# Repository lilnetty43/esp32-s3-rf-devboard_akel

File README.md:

# ESP32-S3 4-Layer RF Development Board

This project is a custom 4-layer development board built around the ESP32-S3. I designed the board to expand my PCB design experience into an RF-aware layout, multi-layer stackup design, controlled-impedance USB routing, and manufacturing preparation.

My board include native USB-C programming and power, 5 V-to-3.3 V regulation, GPIO breakout headers, BOOT and RESET controls, protection circuitry, test points, and a programmable RGB status LED.

*KiCad-generated 3D render of the ESP32-S3 development board.*

---

## Project Overview

The ESP32-S3 module provides Wi-Fi and Bluetooth connectivity using its integrated PCB antenna. The board exposes the ESP32-S3 GPIO through two headers while providing the supporting power, USB, programming, reset, and protection circuitry needed for standalone development.

A 4-layer PCB stackup was used to provide dedicated ground and power planes while maintaining short return paths and supporting controlled-impedance routing for the native USB interface.

---

## Details

- **MCU:** ESP32-S3 [LINK]
- **PCB:** 4-layer, 1.6 mm
- **USB:** USB-C with native ESP32-S3 USB programming[LINK]
- **USB Routing:** 90 Ω differential impedance target for D+/D−
- **Power Input:** 5V USB
- **Regulation:** 5V to 3.3V using LD1117S33 [LINK]
- **GPIO:** Dual breakout headers
- **Controls:** BOOT/RESET pushbuttons [LINK]
- **Protection:** USB ESD protection [LINK]
- **Status:** Programmable RGB LED [LINK]
- **Debugging:** Dedicated test points for important power and signal nets for debugging/checking

---

## PCB Stackup

The board uses a 4-layer stackup:
- **L1/F.Cu:** Components and signals
- **L2/In1.Cu:** Solid GND
- **L3/In2.Cu:** 3.3 V power 
- **L4/B.Cu:** Secondary signal routing

The stackup was configured around the intended JLCPCB manufacturing process rather than using KiCad's default layer construction.

---

## PCB Design Highlights [FIX!!!]

*Top PCB layout showing component placement and routed signals.*

---

## USB Differential Pair

The ESP32-S3 native USB interface was one of the primary high-speed layout considerations for this project.

The D+ and D− pair was routed using dimensions calculated for the selected 4-layer manufacturing stackup:

- **Target differential impedance:** 90 Ω
- **Reference plane:** L2 / In1.Cu GND
- **Routing layer:** L1 / F.Cu
- **Trace width:** 0.3051 mm
- **Pair spacing:** 0.1501 mm
- **Series termination:** 22 Ω

I utilized the JLCPCB resources and calculator to help determine this targeted impedance.

*USB D+ and D− differential-pair routing between the USB-C interface and ESP32-S3.*

---

## Tools

- KiCad — schematic capture, PCB layout, routing, and 3D visualization
- JLCPCB impedance calculator (USB differential-pair geometry)
- Manufacturer datasheets and reference designs
- Git/GitHub
---

## Manufacturing

The PCB design and manufacturing files have been prepared for fabrication through JLCPCB.

Manufacturing/order status: **Pending**

---

## What I Learned

This was a fun project to dive into. i have expanded on my previous PCB work by introducing new design factors like:

- Working with an RF module and PCB antenna keepout requirements
- Revisiting USB differential-pair routing and controlled impedance
- Revisiting the design around dedicated internal ground and power planes
- Applying manufacturer-specific PCB constraints
- Preparing a complete PCB design for external fabrication

---

## Repo Structure

```text
esp32-s3-rf-devboard/
├── README.md
├── docs/
│   └── images/
│       ├── 3d_renders/
│       ├── pcb_routing/
│       └── schematic/
├── fabrication/
│   └── JLCPCB_REV1/
├── hardware/
│   ├── ESP32S3_RF_DevBoard.kicad_pro
│   ├── ESP32S3_RF_DevBoard.kicad_sch
│   └── ESP32S3_RF_DevBoard.kicad_pcb
└── manufacturing (PENDING)/

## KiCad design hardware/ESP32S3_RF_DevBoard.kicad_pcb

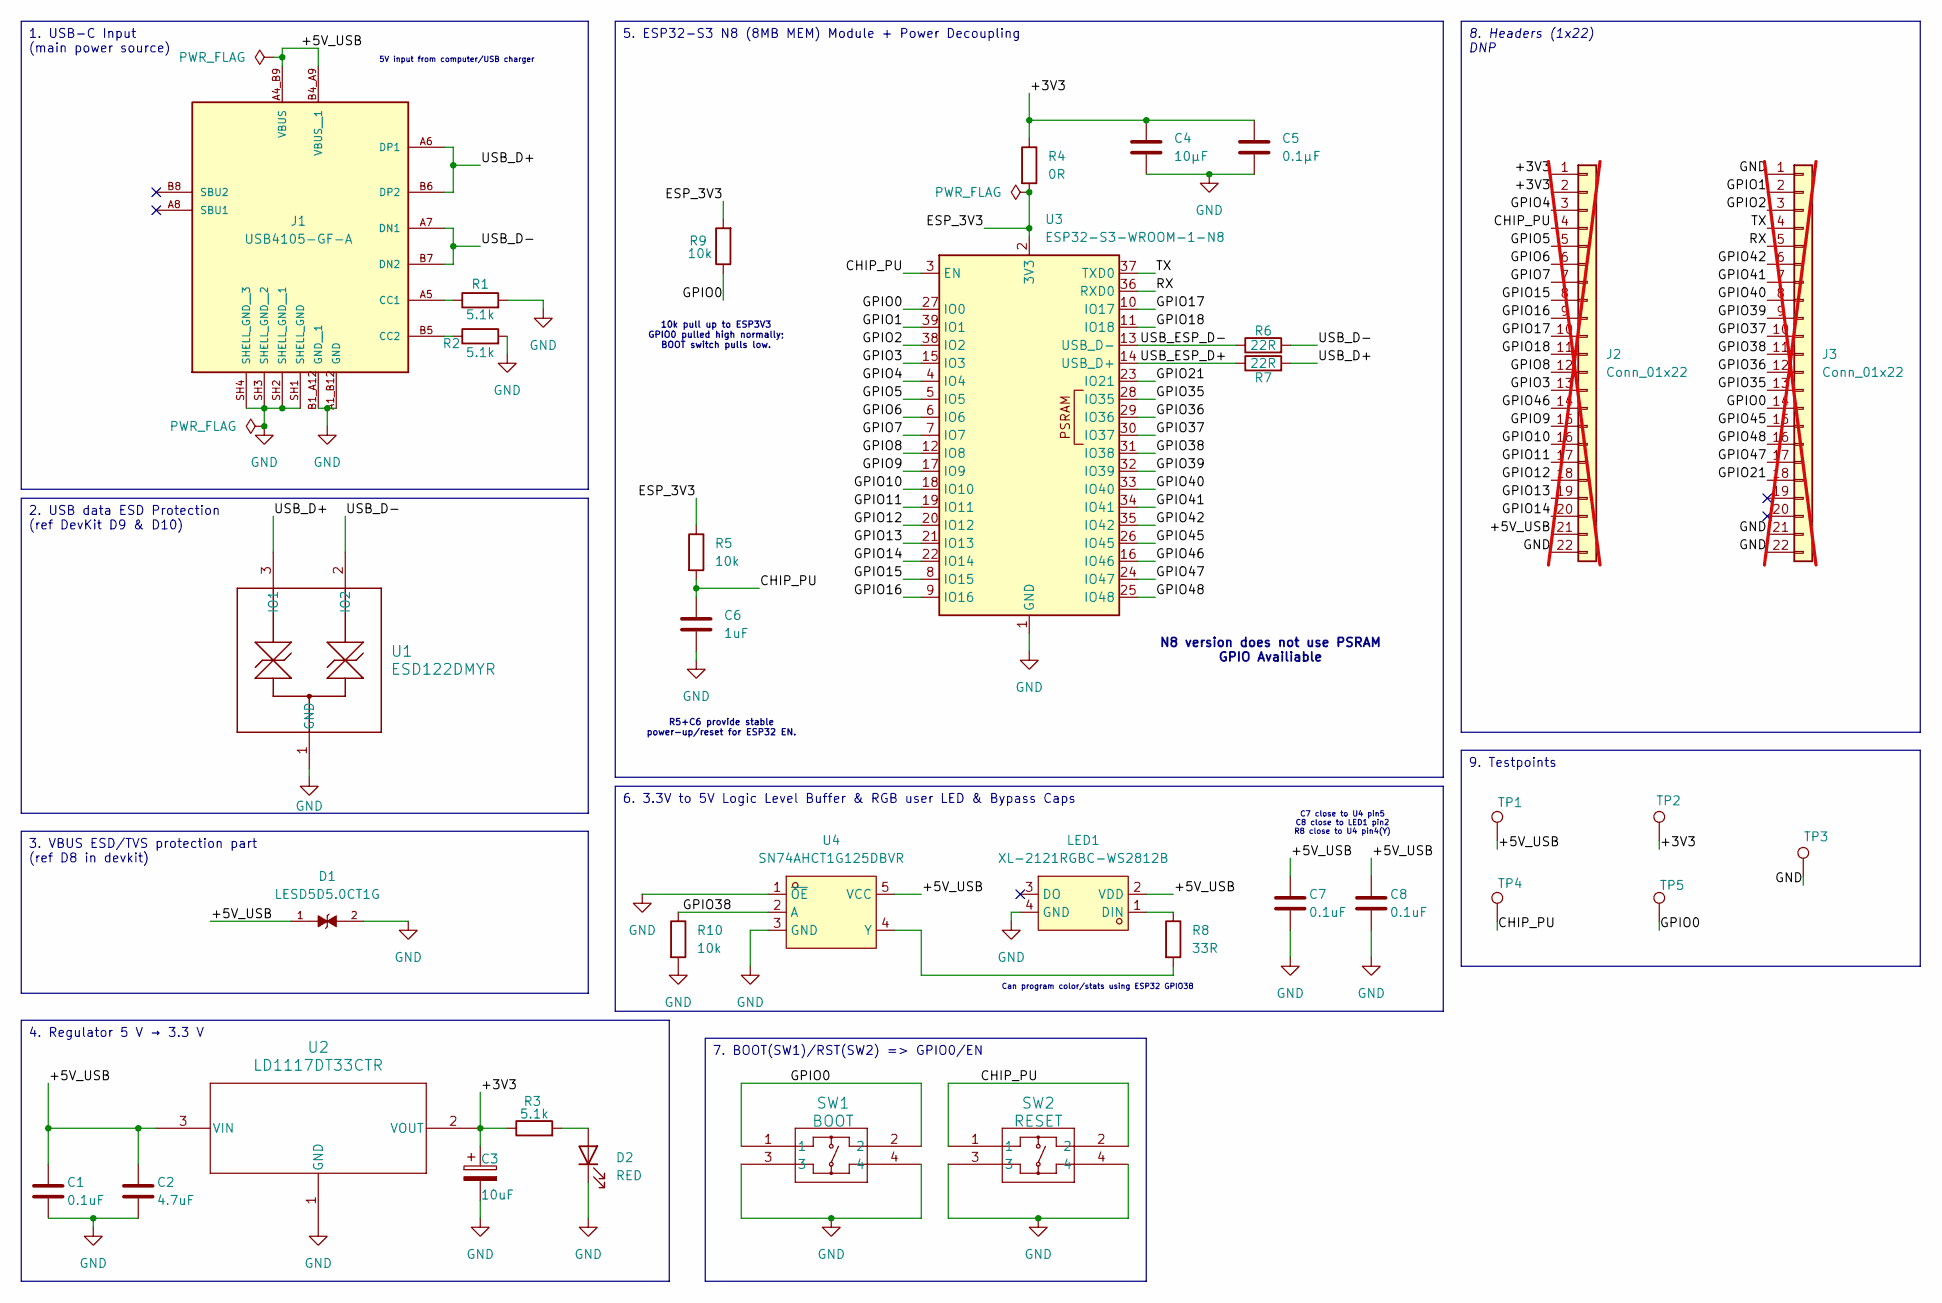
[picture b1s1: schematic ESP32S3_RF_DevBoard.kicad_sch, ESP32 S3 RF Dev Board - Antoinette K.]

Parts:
C1, C7, C8: 0.1uF; C_0603_1608Metric; MPN 0603B104K160CT; LCSC C80516
C2: 4.7uF; C_0805_2012Metric; MPN FS21B475K160EIG; LCSC C2929196
C3: 10uF; CP_EIA-3528-21_Kemet-B; MPN T491B106M016AT; LCSC/JLCPCB C118754
C4: 10µF; C_0603_1608Metric; Voltage 25V; Tolerance ±20%; MPN GRM188R61E106MA73D; LCSC/JLCPCB C91606
C5: 0.1µF; C_0603_1608Metric; Voltage 50V; Tolerance ±10%; MPN CL10B104KB8NNNC; LCSC/JLCPCB C1591
C6: 1uF; C_0805_2012Metric; Voltage 16V; Tolerance ±10%; MPN CL21B105KOFNNNE; LCSC/JLCPCB C24123
D1: LESD5D5.0CT1G; TVS_LESD5D5.0CT1G; PARTREV O
D2: RED; LED_0603_1608Metric; MPN KT-0603R; LCSC/JCLPCB C2286
J1: USB4105-GF-A; GCT_USB4105-GF-A; PARTREV B4
J2, J3: Conn_01x22; PinHeader_1x22_P2.54mm_Vertical; MPN PZ254V-11-22P; JLCPCB/LCSC C22465881; not fitted
LED1: XL-2121RGBC-WS2812B; LED-SMD_4P-L2.1-W2.1-BR_XL-2121RGBC-WS2812B; MPN XL-2121RGBC-2812B; LCSC Part C5349957
R1, R2: 5.1k; R_0603_1608Metric; JLCPCB/LCSC C14677
R3: 5.1k; R_0603_1608Metric; Tolerance ±5%
R4: 0R; R_0603_1608Metric; LCSC/JLCPCB C21189
R5, R9, R10: 10k; R_0603_1608Metric; MPN 0603WAF1002T5E; LCSC/JLCPCB C25804
R6, R7: 22R; R_0603_1608Metric; Tolerance ±1%; MPN 0603WAF220JT5E; LCSC/JLCPCB C23345
R8: 33R; R_0603_1608Metric; MPN 0603WAF330JT5E; LCSC/JLCPCB C23140
SW1: BOOT; SKRPANE010_AAL; MPN SKRPANE010; JLCPCB/LCSC C470426
SW2: RESET; SKRPANE010_AAL; MPN SKRPANE010; JLCPCB/LCSC C470426
TP1, TP2, TP3: TestPoint; TestPoint_Pad_D1.5mm
TP4, TP5: TestPoint; TestPoint_Pad_D1.0mm
U1: ESD122DMYR; DMY0003A
U2: LD1117DT33CTR; DPAK_STM
U3: ESP32-S3-WROOM-1-N8; ESP32-S3-WROOM-1
U4: SN74AHCT1G125DBVR; SOT-23-5_L3.0-W1.7-P0.95-LS2.8-BR; MPN SN74AHCT1G125DBVR; LCSC Part C7484

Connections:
/+3V3: C3.1, C4.1, C5.1, J2.1, J2.2, R3.1, R4.1, TP2.1 (1_1), U2.2 (VOUT)
/+5V_USB: C1.1, C2.1, C7.1, C8.1, D1.1, J1.A4_B9 (VBUS), J1.B4_A9 (VBUS__1), J2.21, LED1.2 (VDD), TP1.1 (1_1), U2.3 (VIN), U4.5 (VCC)
/CHIP_PU: C6.1, J2.4, R5.2, SW2.1, SW2.2, TP4.1 (1_1), U3.3 (EN)
/ESP_3V3: R4.2, R5.1, R9.2, U3.2 (3V3)
/GPIO0: J3.14, R9.1, SW1.1, SW1.2, TP5.1 (1_1), U3.27 (IO0)
/GPIO1: J3.2, U3.39 (IO1)
/GPIO2: J3.3, U3.38 (IO2)
/GPIO3: J2.13, U3.15 (IO3)
/GPIO4: J2.3, U3.4 (IO4)
/GPIO5: J2.5, U3.5 (IO5)
/GPIO6: J2.6, U3.6 (IO6)
/GPIO7: J2.7, U3.7 (IO7)
/GPIO8: J2.12, U3.12 (IO8)
/GPIO9: J2.15, U3.17 (IO9)
/GPIO10: J2.16, U3.18 (IO10)
/GPIO11: J2.17, U3.19 (IO11)
/GPIO12: J2.18, U3.20 (IO12)
/GPIO13: J2.19, U3.21 (IO13)
/GPIO14: J2.20, U3.22 (IO14)
/GPIO15: J2.8, U3.8 (IO15)
/GPIO16: J2.9, U3.9 (IO16)
/GPIO17: J2.10, U3.10 (IO17)
/GPIO18: J2.11, U3.11 (IO18)
/GPIO21: J3.18, U3.23 (IO21)
/GPIO35: J3.13, U3.28 (IO35)
/GPIO36: J3.12, U3.29 (IO36)
/GPIO37: J3.10, U3.30 (IO37)
/GPIO38: J3.11, R10.1, U3.31 (IO38), U4.2 (A)
/GPIO39: J3.9, U3.32 (IO39)
/GPIO40: J3.8, U3.33 (IO40)
/GPIO41: J3.7, U3.34 (IO41)
/GPIO42: J3.6, U3.35 (IO42)
/GPIO45: J3.15, U3.26 (IO45)
/GPIO46: J2.14, U3.16 (IO46)
/GPIO47: J3.17, U3.24 (IO47)
/GPIO48: J3.16, U3.25 (IO48)
/RX: J3.5, U3.36 (RXD0)
/TX: J3.4, U3.37 (TXD0)
/USB_D+: J1.A6 (DP1), J1.B6 (DP2), R7.2, U1.3 (IO1)
/USB_D-: J1.A7 (DN1), J1.B7 (DN2), R6.2, U1.2 (IO2)
/USB_ESP_D+: R7.1, U3.14 (USB_D+)
/USB_ESP_D-: R6.1, U3.13 (USB_D-)
GND: C1.2, C2.2, C3.2, C4.2, C5.2, C6.2, C7.2, C8.2, D1.2, D2.1 (K), J1.A1_B12 (GND), J1.B1_A12 (GND__1), J1.SH1 (SHELL_GND), J1.SH2 (SHELL_GND__1), J1.SH3 (SHELL_GND__2), J1.SH4 (SHELL_GND__3), J2.22, J3.1, J3.21, J3.22, LED1.4 (GND), R1.2, R2.2, R10.2, SW1.3, SW1.4, SW2.3, SW2.4, TP3.1 (1_1), U1.1 (GND), U2.1 (GND), U3.1 (GND), U3.40 (GND), U3.41 (GND), U4.1 (~OE), U4.3 (GND)
unnamed: D2.2 (A), R3.2
unnamed: J1.A5 (CC1), R1.1
unnamed: J1.B5 (CC2), R2.1
unnamed: LED1.1 (DIN), R8.1
unnamed: R8.2, U4.4 (Y)

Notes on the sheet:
C7 close to U4 pin5 C8 close to LED1 pin2 R8 close to U4 pin4(Y)
10k pull up to ESP3V3 GPIO0 pulled high normally; BOOT switch pulls low.
N8 version does not use PSRAM GPIO Availiable
5V input from computer/USB charger
R5+C6 provide stable power-up/reset for ESP32 EN.
Can program color/stats using ESP32 GPIO38
3. VBUS ESD/TVS protection part (ref D8 in devkit)
8. Headers (1x22) DNP
4. Regulator 5 V → 3.3 V
7. BOOT(SW1)/RST(SW2) => GPIO0/EN
1. USB-C Input (main power source)
6. 3.3V to 5V Logic Level Buffer & RGB user LED & Bypass Caps
9. Testpoints
5. ESP32-S3 N8 (8MB MEM) Module + Power Decoupling
2. USB data ESD Protection (ref DevKit D9 & D10)

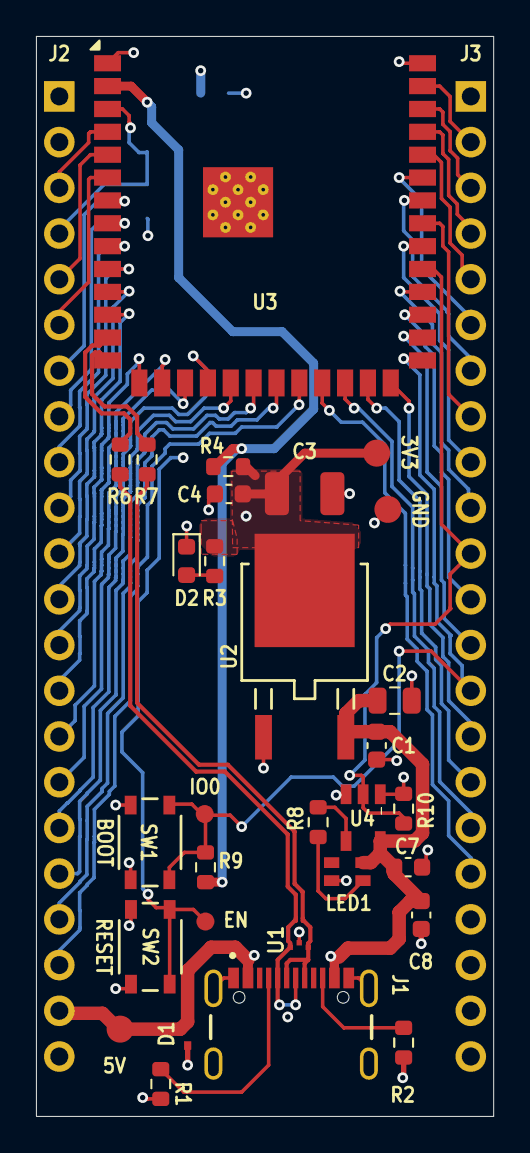
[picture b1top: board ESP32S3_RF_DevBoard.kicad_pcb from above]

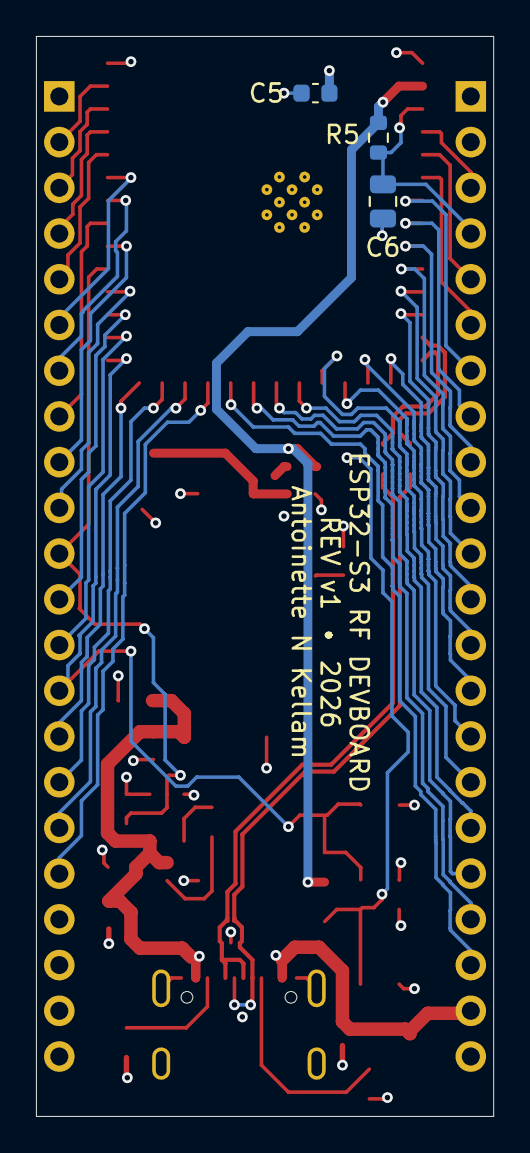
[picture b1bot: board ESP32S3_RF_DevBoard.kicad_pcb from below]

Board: 4 copper layers, 25.4 x 60.0 mm, 35 parts (3 on the bottom side), 48 nets.

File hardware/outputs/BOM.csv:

Reference,Component,Manufacturer,Manufacturer Part Number,LCSC Part Number,Quantity,Unit Price (USD),Description,Notes,Link
"C1, C5, C7, C8",0.1uF,,,,4,,0603 ceramic capacitor,Decoupling capacitor,
C2,4.7uF,,,,1,,0805 capacitor,,
C3,10uF,,,,1,,EIA 3528-21 capacitor,Bulk capacitance,
C4,10uF,,,,1,,0603 ceramic capacitor,Bulk/decoupling capacitance,
C6,1uF,,,,1,,0805 ceramic capacitor,,
"R1, R2, R3",5.1k,,,,3,,0603 resistor,,
"R5, R9, R10",10k,,,,3,,0603 resistor,,
"R6, R7",22R,,,,2,,0603 resistor,USB D+/D- series resistors,
R4,0R,,,,1,,0603 resistor,0-ohm resistor,
R8,33R,,,,1,,0603 resistor,,
D1,LESD5D5.0CT1G,,,,1,,TVS protection diode,,
D2,RED,,,,1,,0603 red LED,Status LED,
U1,ESD122DMYR,,,,1,,USB ESD protection device,USB D+/D- protection,
U2,LD1117DT33CTR,STMicroelectronics,LD1117DT33CTR,,1,,3.3 V linear regulator,5 V to 3.3 V regulation,
U3,ESP32-S3-WROOM-1-N8,Espressif,ESP32-S3-WROOM-1-N8,,1,,ESP32-S3 Wi-Fi/Bluetooth module,Main MCU and RF module,
U4,SN74AHCT1G125DBVR,,,,1,,Single buffer/level interface,,
SW1,BOOT,,,,1,,Momentary pushbutton,BOOT control,
SW2,RESET,,,,1,,Momentary pushbutton,RESET control,
LED1,XL-2121RGBC-WS2812B,,,,1,,Addressable RGB LED,Programmable status LED,
"J2, J3",Conn_01x22,,,,2,,1x22 2.54 mm vertical headers,GPIO breakout headers,
J1,USB4105-GF-A,GCT,USB4105-GF-A,C3020560,1,,USB Type-C receptacle,USB power and native USB interface,
